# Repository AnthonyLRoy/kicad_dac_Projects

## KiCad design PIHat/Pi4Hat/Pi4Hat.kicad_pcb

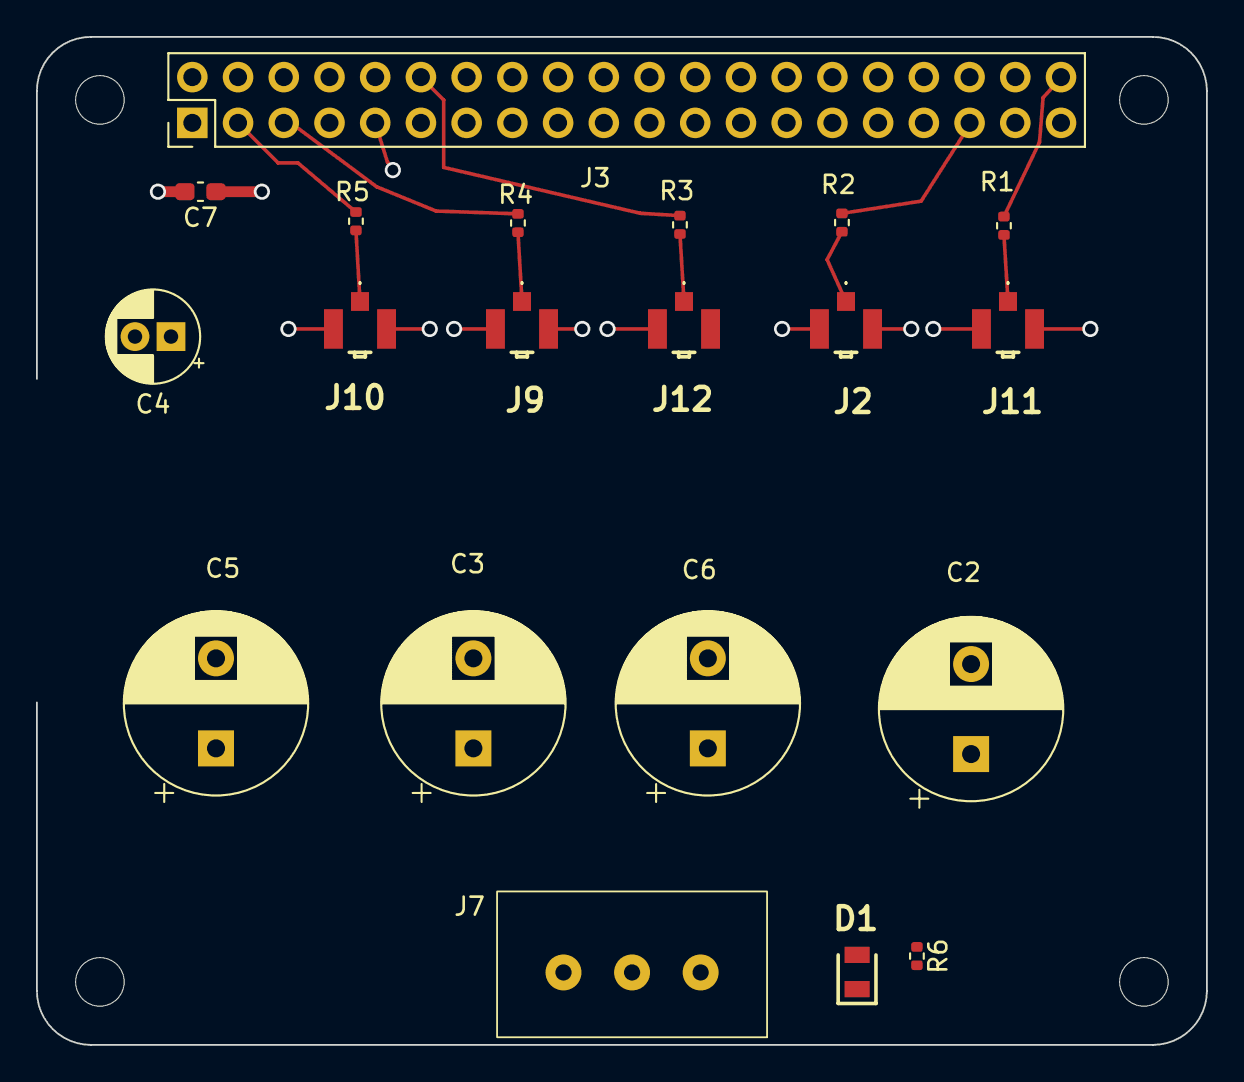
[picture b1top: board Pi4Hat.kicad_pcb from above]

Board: 4 copper layers, 65.0 x 56.0 mm, 24 parts (0 on the bottom side), 14 nets.

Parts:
C2, C3, C5, C6: 470u; CP_Radial_D10.0mm_P5.00mm
C4: 4u7; CP_Radial_D5.0mm_P2.00mm
C7: 0u1; C_0603_1608Metric_Pad1.08x0.95mm_HandSolder
D1: LS_R976; LEDC2012X40N
J2, J9, J10, J11, J12: U.FL-R-SMT-1_80_; UFLRSMT180
J3: 70246-4001; PinHeader_2x20_P2.54mm_Vertical
J7: Conn_01x03_Socket; PCB Wired Socket
MH1, MH2, MH3, MH4: MountingHole_2.7mm_M2.5
R1, R2, R3, R4, R5: 22; R_0402_1005Metric
R6: 1k; R_0402_1005Metric

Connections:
+3.3V: J3.1, J3.17
+5V: C2.1, C3.1, C4.1, C5.1, C6.1, C7.1, D1.2 (A), J3.2, J3.4, J7.1, J7.2
/GPIO2/SDA1: J3.3, R5.1
/GPIO3/SCL1: J3.5, R4.1
/GPIO18/I2S BCL: J3.12, R3.1
/GPIO19/I2S LRCK: J3.35, R2.1
/GPIO21/I2S DOUT: J3.40, R1.1
GND: C2.2, C3.2, C4.2, C5.2, C6.2, C7.2, J2.2 (GND_1), J2.3 (GND_2), J3.6, J3.9, J3.14, J3.20, J3.25, J3.30, J3.34, J3.39, J7.3, J9.2 (GND_1), J9.3 (GND_2), J10.2 (GND_1), J10.3 (GND_2), J11.2 (GND_1), J11.3 (GND_2), J12.2 (GND_1), J12.3 (GND_2), R6.1
unnamed: D1.1 (K), R6.2
unnamed: J2.1 (SIG), R2.2
unnamed: J9.1 (SIG), R4.2
unnamed: J10.1 (SIG), R5.2
unnamed: J11.1 (SIG), R1.2
unnamed: J12.1 (SIG), R3.2

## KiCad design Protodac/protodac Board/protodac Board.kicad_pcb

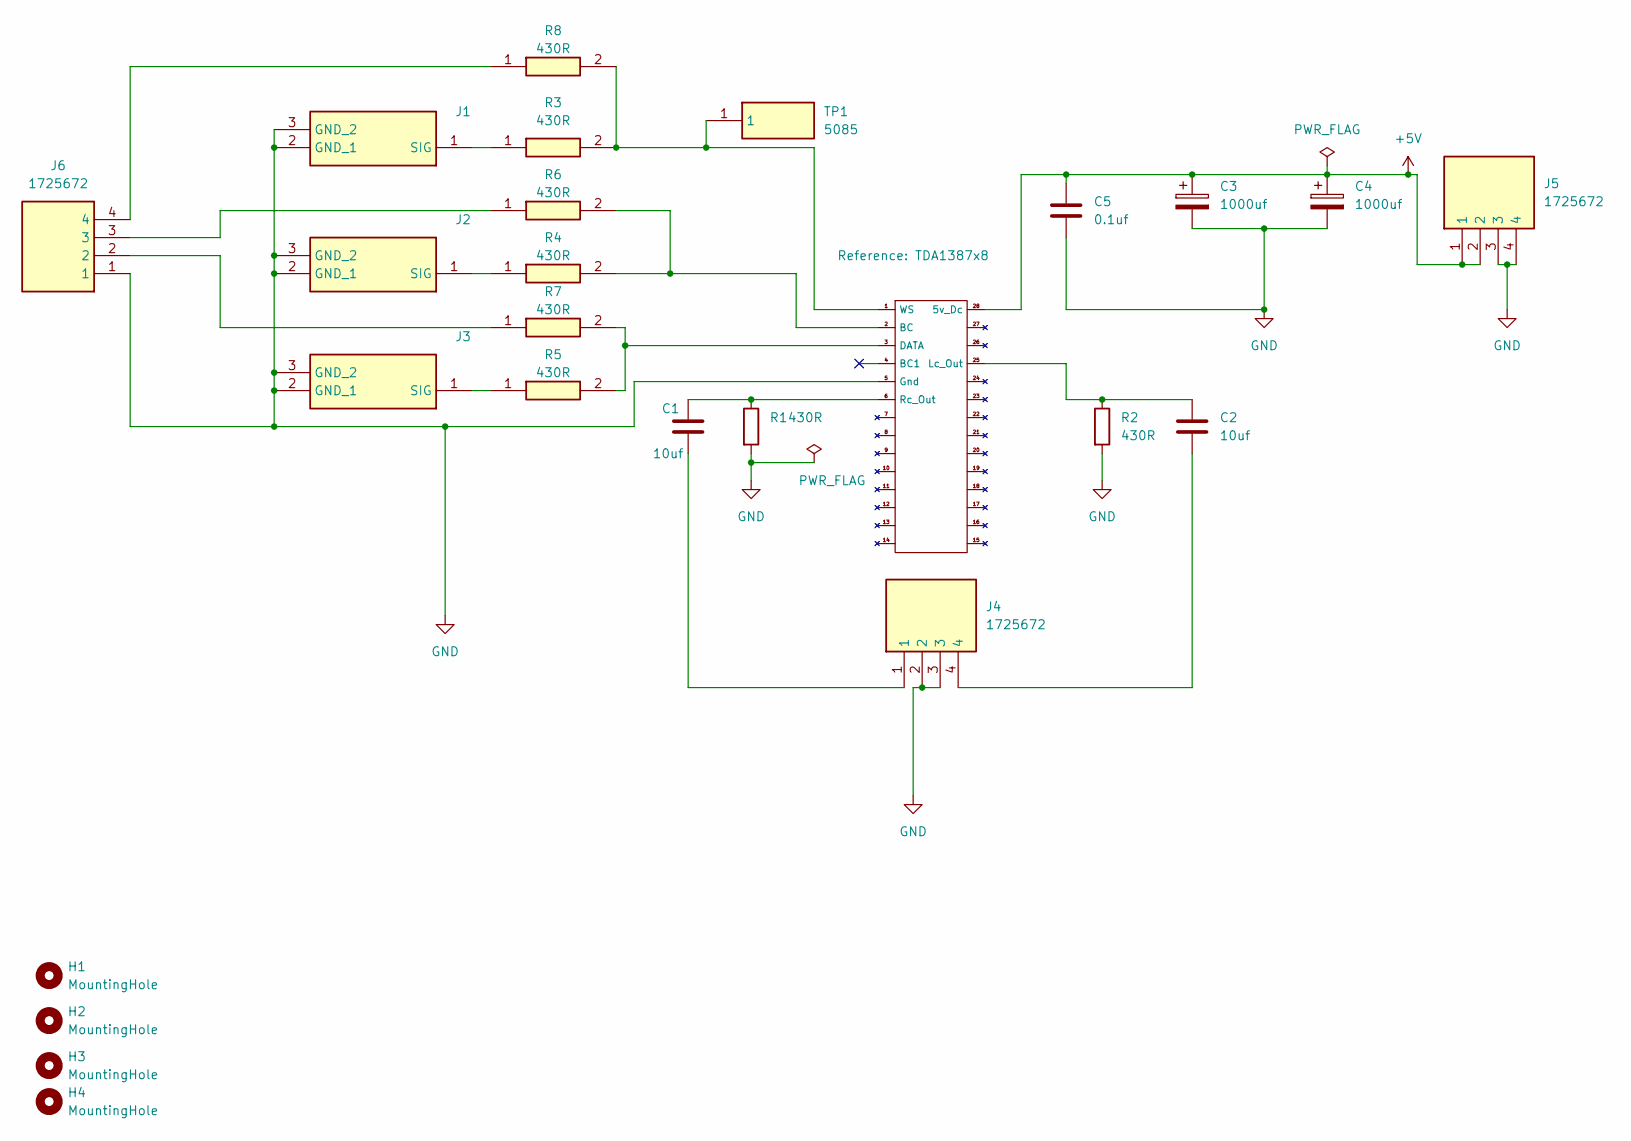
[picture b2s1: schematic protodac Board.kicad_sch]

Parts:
C1, C2: 10uf; Clarity Cap
C3, C4: 1000uf; Audio Note Kaisei POLAR
C5: 0.1uf; K104K20X7RK53H5G
H1, H2, H3, H4: MountingHole; MountingHole_2.7mm_M2.5
J1, J2, J3: U.FL-R-SMT-1_80_; UFLRSMT180; Manufacturer_Part_Number U.FL-R-SMT-1(80)
J4, J5, J6: 1725672; Mouser Part Number 651-1725672
R1, R2: 430R; Y0007400R000V0L
R3, R4, R5, R6, R7, R8: 430R; ERJH3; Mouser Part Number 667-ERJ-H3EF4300V
TDA1387x8: TDA1387
TP1: 5085; Mouser Part Number 534-5085

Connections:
+5V: C3.1, C4.1, C5.1, J5.1, J5.2, TDA1387x8.28 (5v_Dc)
GND: C3.2, C4.2, C5.2, J1.2 (GND_1), J1.3 (GND_2), J2.2 (GND_1), J2.3 (GND_2), J3.2 (GND_1), J3.3 (GND_2), J4.2, J4.3, J5.3, J5.4, J6.1, R1.2, R2.2, TDA1387x8.5 (Gnd)
unnamed: C1.2, J4.1
unnamed: C2.2, J4.4
unnamed: J1.1 (SIG), R3.1
unnamed: J2.1 (SIG), R4.1
unnamed: J3.1 (SIG), R5.1
unnamed: J6.2, R7.1
unnamed: J6.3, R6.1
unnamed: J6.4, R8.1
unnamed: R4.2, R6.2, TDA1387x8.2 (BC)
unnamed: R5.2, R7.2, TDA1387x8.3 (DATA)
unnamed: C2.1, R2.1, TDA1387x8.25 (Lc_Out)
unnamed: C1.1, R1.1, TDA1387x8.6 (Rc_Out)
unnamed: R3.2, R8.2, TDA1387x8.1 (WS), TP1.1

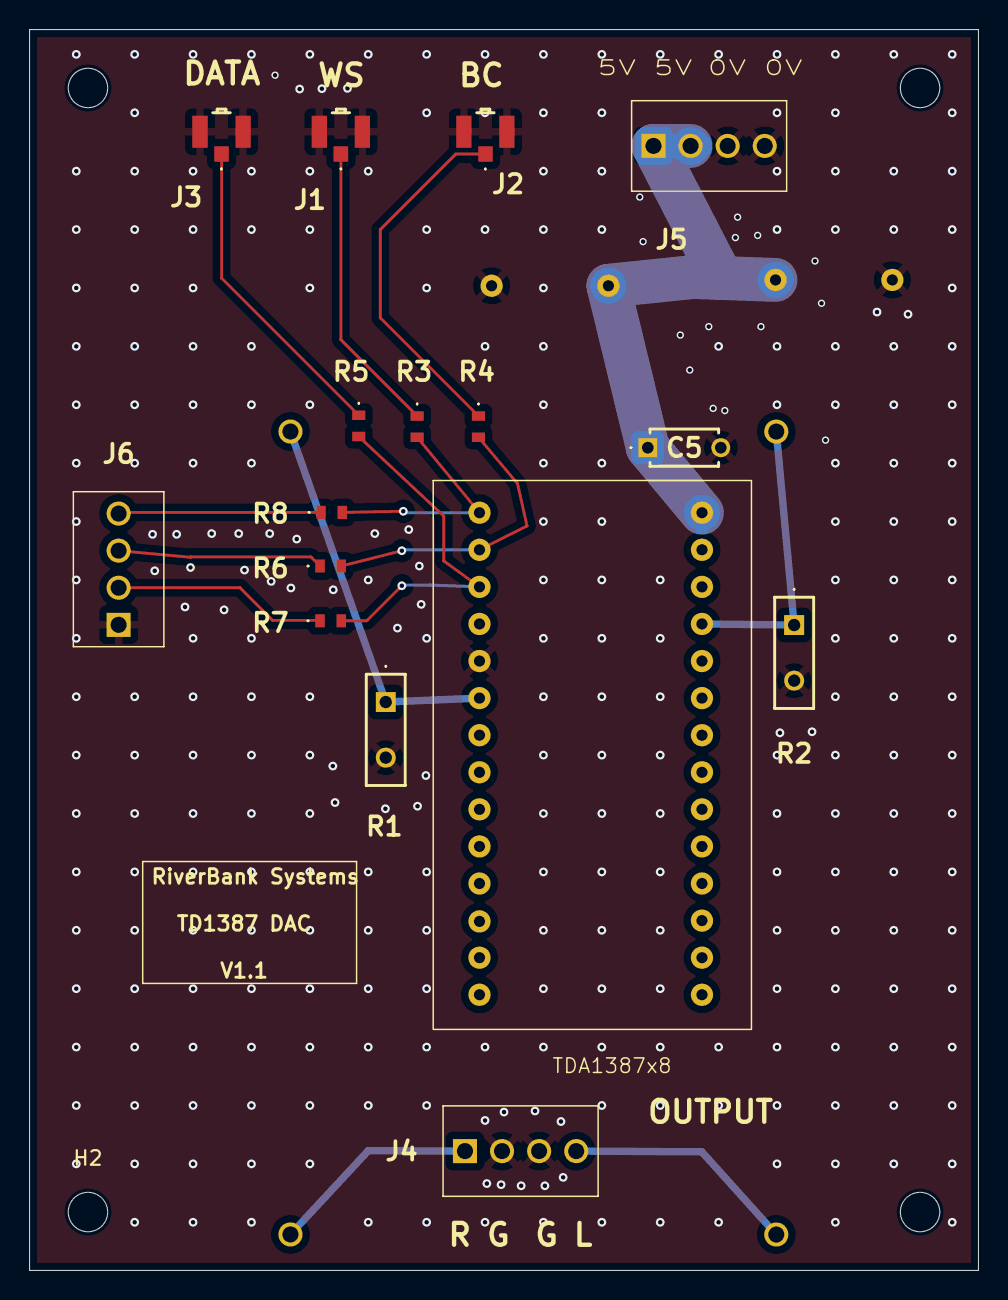
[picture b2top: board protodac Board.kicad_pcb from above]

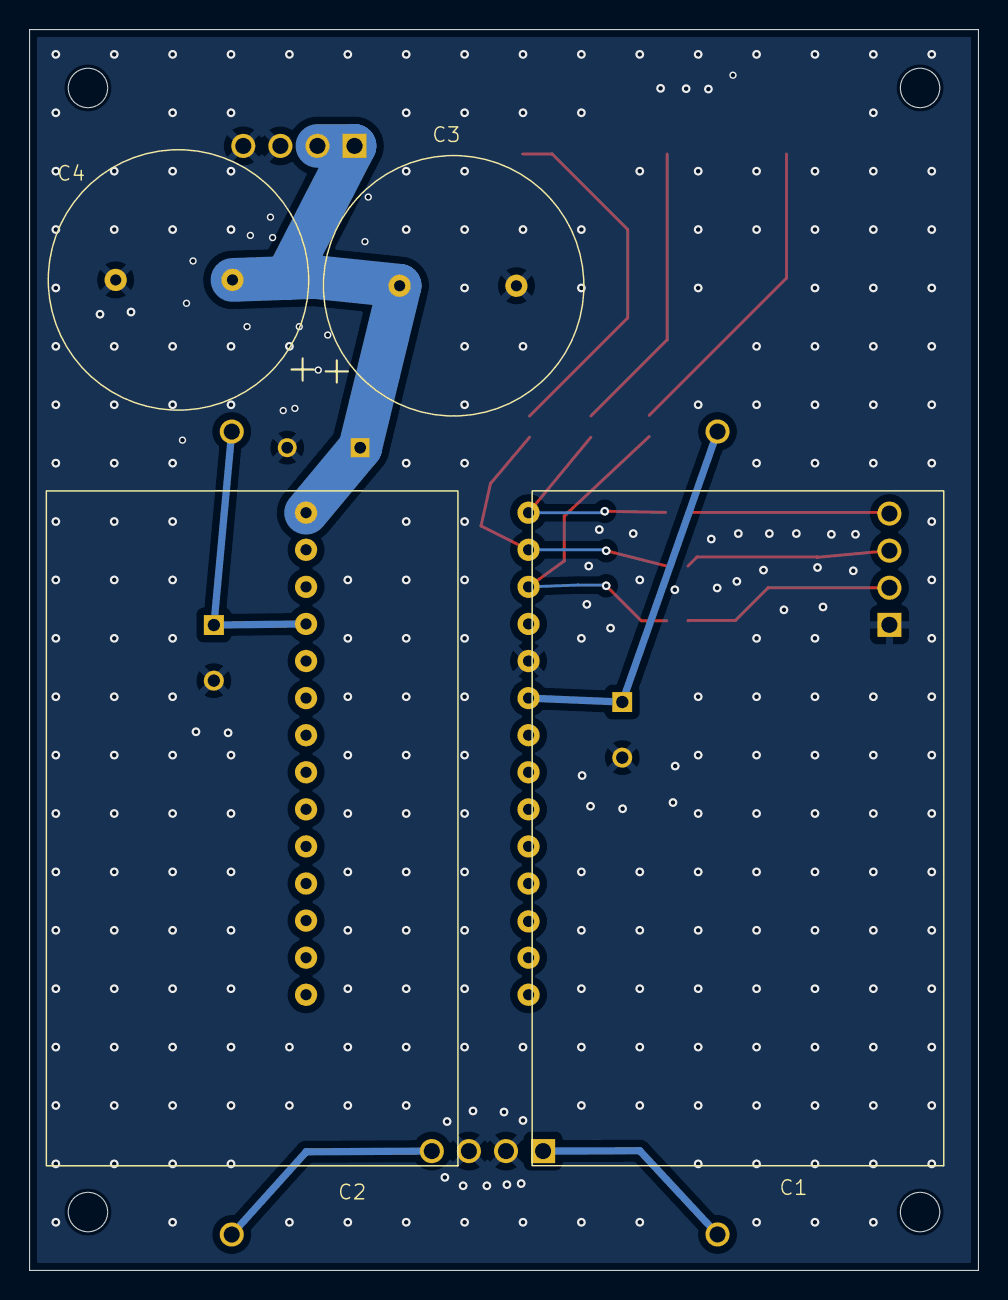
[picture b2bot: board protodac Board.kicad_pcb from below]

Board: 2 copper layers, 65.0 x 85.0 mm, 24 parts (4 on the bottom side), 15 nets.

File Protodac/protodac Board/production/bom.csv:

Designator,Footprint,Quantity,Value,LCSC Part #
"C1, C2",Clarity Cap,2,10uf,
"C3, C4",Audio Note Kaisei POLAR,2,1000uf,
C5,K104K20X7RK53H5G,1,0.1uf,
"H1, H2, H3, H4",MountingHole_2.7mm_M2.5,4,MountingHole,
"J1, J2, J3",UFLRSMT180,3,U.FL-R-SMT-1_80_,
"J4, J5, J6",1725672,3,1725672,
"R1, R2",Y0007400R000V0L,2,430R,
"R3, R4, R5, R6, R7, R8",ERJH3,6,430R,
TDA1387X8,TDA1387,1,~,

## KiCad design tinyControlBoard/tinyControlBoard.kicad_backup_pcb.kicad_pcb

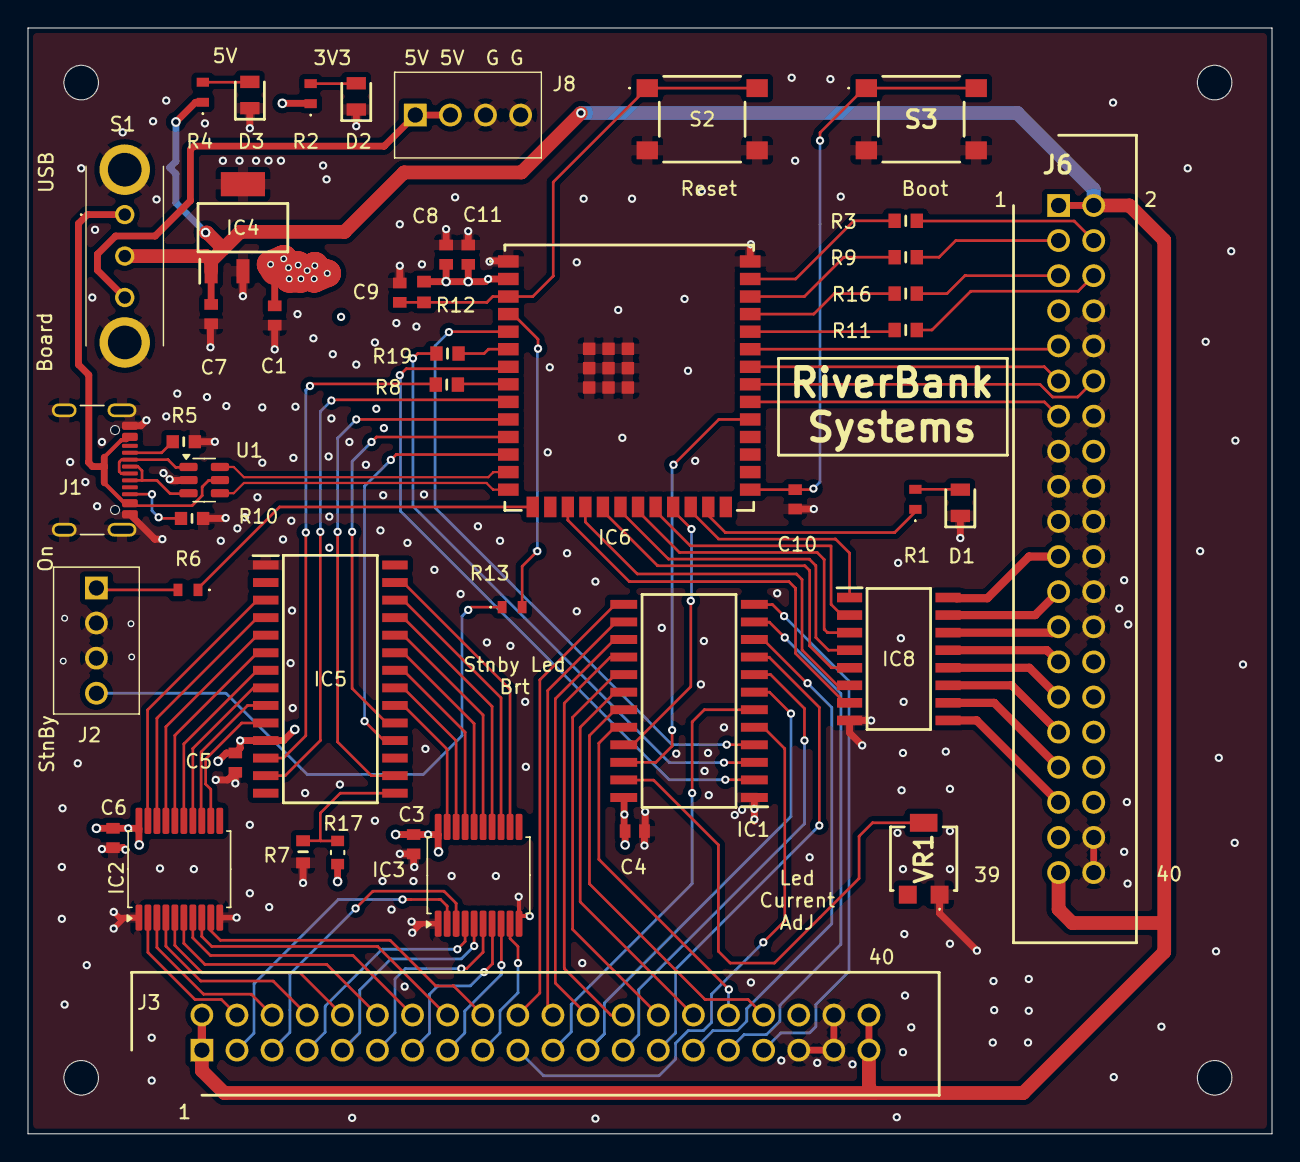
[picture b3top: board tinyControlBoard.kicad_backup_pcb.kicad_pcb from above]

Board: 4 copper layers, 90.0 x 80.0 mm, 50 parts (0 on the bottom side), 110 nets.

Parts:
C1: u33; CAPC1608X90N
C3, C4, C5, C6, C9, C10, C11: 0u1; CAPC1608X87N
C7: u47; CAPC1608X90N
C8: 10u; CAPC1608X90N
D1, D2: LG_R971-KN-1; LEDC2012X80N
D3: LS_R976; LEDC2012X40N
H1, H2, H3, H4: MountingHole; MountingHole_2.5mm
IC1: STP16CPC26MTR; SOIC127P1032X265-24N
IC2, IC3: MAX6818EAP+T; SSOP-20_5.3x7.2mm_P0.65mm
IC4: LM3940IMPX-3.3; SOT230P700X180-4N
IC5: MCP23018-E_SO; SOIC127P1030X265-28N
IC6: ESP32-S3-WROOM-1U-N16; ESP32S3WROOM1UN16
IC8: ULN2003ANSRE4; SOIC127P780X200-16N
J1: USB_C_Receptacle_USB2.0_16P; USB_C_Receptacle_GCT_USB4105-xx-A_16P_TopMnt_Horizontal
J2, J8: 1725672
J3, J6: 70246-4001; SHDR40W64P254_2X20_5842X889X947P
R1, R2: 100R; ERJH3
R3, R8, R9, R11, R16, R19: 22R; RESC1609X55N
R4, R6, R13: 300R; ERJH3
R5, R10: 5K1; RESC1608X55N
R7: MCT0603PD1001DP500; RESC1608X55N
R12: 10K; RESC1608X50N
R17: TNPW060315K0BEEA; RESC1608X60N
S1: EG1206A
S2, S3: 430182043816
U1: USBLC6-2SC6; SOT-23-6
VR1: 3214G-1-103E; 3214G1103E

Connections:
+3V3: C1.1, C3.2, C4.1, C5.1, C6.1, C8.1, C11.1, IC1.24 (VDD), IC2.20 (VCC), IC3.20 (VCC), IC4.3 (OUT), IC5.11 (VDD), IC6.2 (3V3), R2.1, R12.1, R17.1
+5V: C7.1, IC4.1 (IN), J3.1, J3.2, J3.39, J3.40, J6.1, J6.2, J6.39, R4.1, S1.2 (COM)
/BOOT: C10.1, IC6.27 (IO0), S3.1 (COM_1), S3.3 (COM_2)
/Debug RX: J6.6, R11.2
/Debug TX: J6.5, R16.2
/EN: C9.1, IC6.3 (EN), R12.2, S2.1 (COM_1), S2.3 (COM_2)
/GPIO_01: IC6.39 (IO1), R3.1
/GPIO_02: IC6.38 (IO2), R9.1
/GPIO_39: IC6.32 (IO39), J6.13
/IntA: IC5.19 (INTA), IC6.11 (IO18)
/Intb: IC5.18 (INTB), IC6.12 (IO8)
/RXDO: IC6.36 (RXD0), R11.1
/Serial Rx: J6.4, R3.2
/Serial Tx: J6.3, R9.2
/TXDO: IC6.37 (TXD0), R16.1
/USB_5V: J1.A4 (VBUS), J1.A9 (VBUS), J1.B4 (VBUS), J1.B9 (VBUS), S1.1, U1.5 (VBUS)
/USB_N: IC6.13 (IO19), U1.6 (I/O1)
/USB_P: IC6.14 (IO20), U1.4 (I/O2)
/addr_exp: IC5.15 (ADDR), R7.1, R17.2
/app_active: IC6.25 (IO48), R1.1
/btn_in_1: IC2.2 (IN1), J3.4
/btn_in_2: IC2.3 (IN2), J3.6
/btn_in_3: IC2.4 (IN3), J3.8
/btn_in_4: IC2.5 (IN4), J3.10
/btn_in_5: IC2.6 (IN5), J3.12
/btn_in_6: IC2.7 (IN6), J3.14
/btn_in_7: IC2.8 (IN7), J3.16
/btn_in_8: IC2.9 (IN8), J3.18
/btn_in_9: IC3.2 (IN1), J3.3
/btn_in_10: IC3.3 (IN2), J3.5
/btn_in_11: IC3.4 (IN3), J3.7
/btn_in_12: IC3.5 (IN4), J3.9
/btn_in_13: IC3.6 (IN5), J3.11
/btn_in_14: IC3.7 (IN6), J3.13
/btn_in_15: IC3.8 (IN7), J3.15
/btn_in_16: IC3.9 (IN8), J3.17
/btn_l_1: IC2.19 (OUT1), IC5.3 (GPB0)
/btn_l_2: IC2.18 (OUT2), IC5.4 (GPB1)
/btn_l_3: IC2.17 (OUT3), IC5.5 (GPB2)
/btn_l_4: IC2.16 (OUT4), IC5.6 (GPB3)
/btn_l_5: IC2.15 (OUT5), IC5.7 (GPB4)
/btn_l_6: IC2.14 (OUT6), IC5.8 (GPB5)
/btn_l_7: IC2.13 (OUT7), IC5.9 (GPB6)
/btn_l_8: IC2.12 (OUT8), IC5.10 (GPB7)
/btn_l_9: IC3.19 (OUT1), IC5.20 (GPA0)
/btn_l_10: IC3.18 (OUT2), IC5.21 (GPA1)
/btn_l_11: IC3.17 (OUT3), IC5.22 (GPA2)
/btn_l_12: IC3.16 (OUT4), IC5.23 (GPA3)
/btn_l_13: IC3.15 (OUT5), IC5.24 (GPA4)
/btn_l_14: IC3.14 (OUT6), IC5.25 (GPA5)
/btn_l_15: IC3.13 (OUT7), IC5.26 (GPA6)
/btn_l_16: IC3.12 (OUT8), IC5.27 (GPA7)
/dac_on: IC6.22 (IO14), IC8.2 (2B)
/esp_ir_sent: IC6.34 (IO41), J6.11
/gen_relay_2: IC6.18 (IO10), IC8.6 (6B)
/gen_relay_3: IC6.17 (IO9), IC8.7 (7B)
/gen_relay_4: IC6.24 (IO47), IC8.1 (1B)
/led_o_1: IC1.5 (OUT0), J3.19
/led_o_2: IC1.6 (OUT1), J3.21
/led_o_3: IC1.7 (OUT2), J3.23
/led_o_4: IC1.8 (OUT3), J3.25
/led_o_5: IC1.9 (OUT4), J3.27
/led_o_6: IC1.10 (OUT5), J3.29
/led_o_7: IC1.11 (OUT6), J3.31
/led_o_8: IC1.12 (OUT7), J3.33
/led_o_9: IC1.13 (OUT8), J3.20
/led_o_10: IC1.14 (OUT9), J3.22
/led_o_11: IC1.15 (OUT10), J3.24
/led_o_12: IC1.16 (OUT11), J3.26
/led_o_13: IC1.17 (OUT12), J3.28
/led_o_14: IC1.18 (OUT13), J3.30
/led_o_15: IC1.19 (OUT14), J3.34
/led_o_16: IC1.20 (OUT15), J3.32
/mains_out: IC8.12 (5C), J6.29
/mains_power: IC6.19 (IO11), IC8.5 (5B)
/mcp_clk: IC5.12 (SCL), R8.1
/mcp_reset: IC5.16 (~RESET), IC6.10 (IO17)
/mcp_sda: IC5.13 (SDA), IC6.9 (IO16)
/on_led: IC6.15 (IO3), R6.1
/relay_com: IC8.9 (COM), J6.35
/relay_out_1: IC8.16 (1C), J6.21
/relay_out_2: IC8.15 (2C), J6.23
/relay_out_3: IC8.14 (3C), J6.25
/relay_out_4: IC8.13 (4C), J6.27
/relay_out_6: IC8.11 (6C), J6.31
/relay_out_7: IC8.10 (7C), J6.33
/rpi4_data_ready: IC6.35 (IO42), J6.9
/rpi_state: IC6.33 (IO40), J6.12
/screen_on: IC6.21 (IO13), IC8.3 (3B)
/standby_led: IC6.4 (IO4), R13.2
/stp_clk: IC1.3 (CLK), R19.1
/stp_le: IC1.4 (LE), IC6.5 (IO5)
/stp_pwm: IC1.21 (~OE), IC6.23 (IO21)
/stp_sdi: IC1.2 (SDI), IC6.7 (IO7)
/stp_sdo: IC1.22 (SDO), IC6.31 (IO38)
/switch_dac: IC6.20 (IO12), IC8.4 (4B)
GND: C1.2, C3.1, C4.2, C5.2, C6.2, C7.2, C8.2, C9.2, C10.2, C11.2, D1.1 (K), D2.1 (K), D3.1 (K), IC1.1 (GND), IC2.1 (~EN), IC2.10 (GND), IC3.1 (~EN), IC3.10 (GND), IC4.2 (GND_1), IC4.4 (GND_2), IC5.1 (VSS), IC6.1 (GND_1), IC6.40 (GND_2), IC6.41 (GND_3), IC6.42 (GND_4), IC6.43 (GND_5), IC6.44 (GND_6), IC6.45 (GND_7), IC6.46 (GND_8), IC6.47 (GND_9), IC6.48 (GND_10), IC6.49 (GND_11), IC8.8 (E), J1.A1 (GND), J1.A12 (GND), J1.B1 (GND), J1.B12 (GND), J1.S1 (SHIELD), J2.2, J2.3, J3.35, J3.37, J3.38, J6.8, J6.10, J6.14, J6.15, J6.17, J6.18, J6.19, J6.20, J6.22, J6.24, J6.26, J6.38, J6.40, J8.3, J8.4, R5.2, R7.2, R10.2, S1.MH1, S1.MH2, S2.2 (NO_1), S2.4 (NO_2), S3.2 (NO_1), S3.4 (NO_2), U1.2 (GND), VR1.1 (CCW)
unnamed: D1.2 (A), R1.2
unnamed: D2.2 (A), R2.2
unnamed: D3.2 (A), R4.2
unnamed: IC1.23 (R-EXT), VR1.2 (WIPER)
unnamed: IC6.6 (IO6), R19.2
unnamed: IC6.8 (IO15), R8.2
unnamed: J1.A5 (CC1), R5.1
unnamed: J1.B5 (CC2), R10.1
unnamed: J1.A6 (D+), J1.B6 (D+), U1.3 (I/O2)
unnamed: J1.A7 (D-), J1.B7 (D-), U1.1 (I/O1)
unnamed: J2.1, R6.2
unnamed: J2.4, R13.1
VCC: J8.1, J8.2, S1.3
